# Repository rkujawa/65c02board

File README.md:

# 65c02board
Another 65c02 hobby computer

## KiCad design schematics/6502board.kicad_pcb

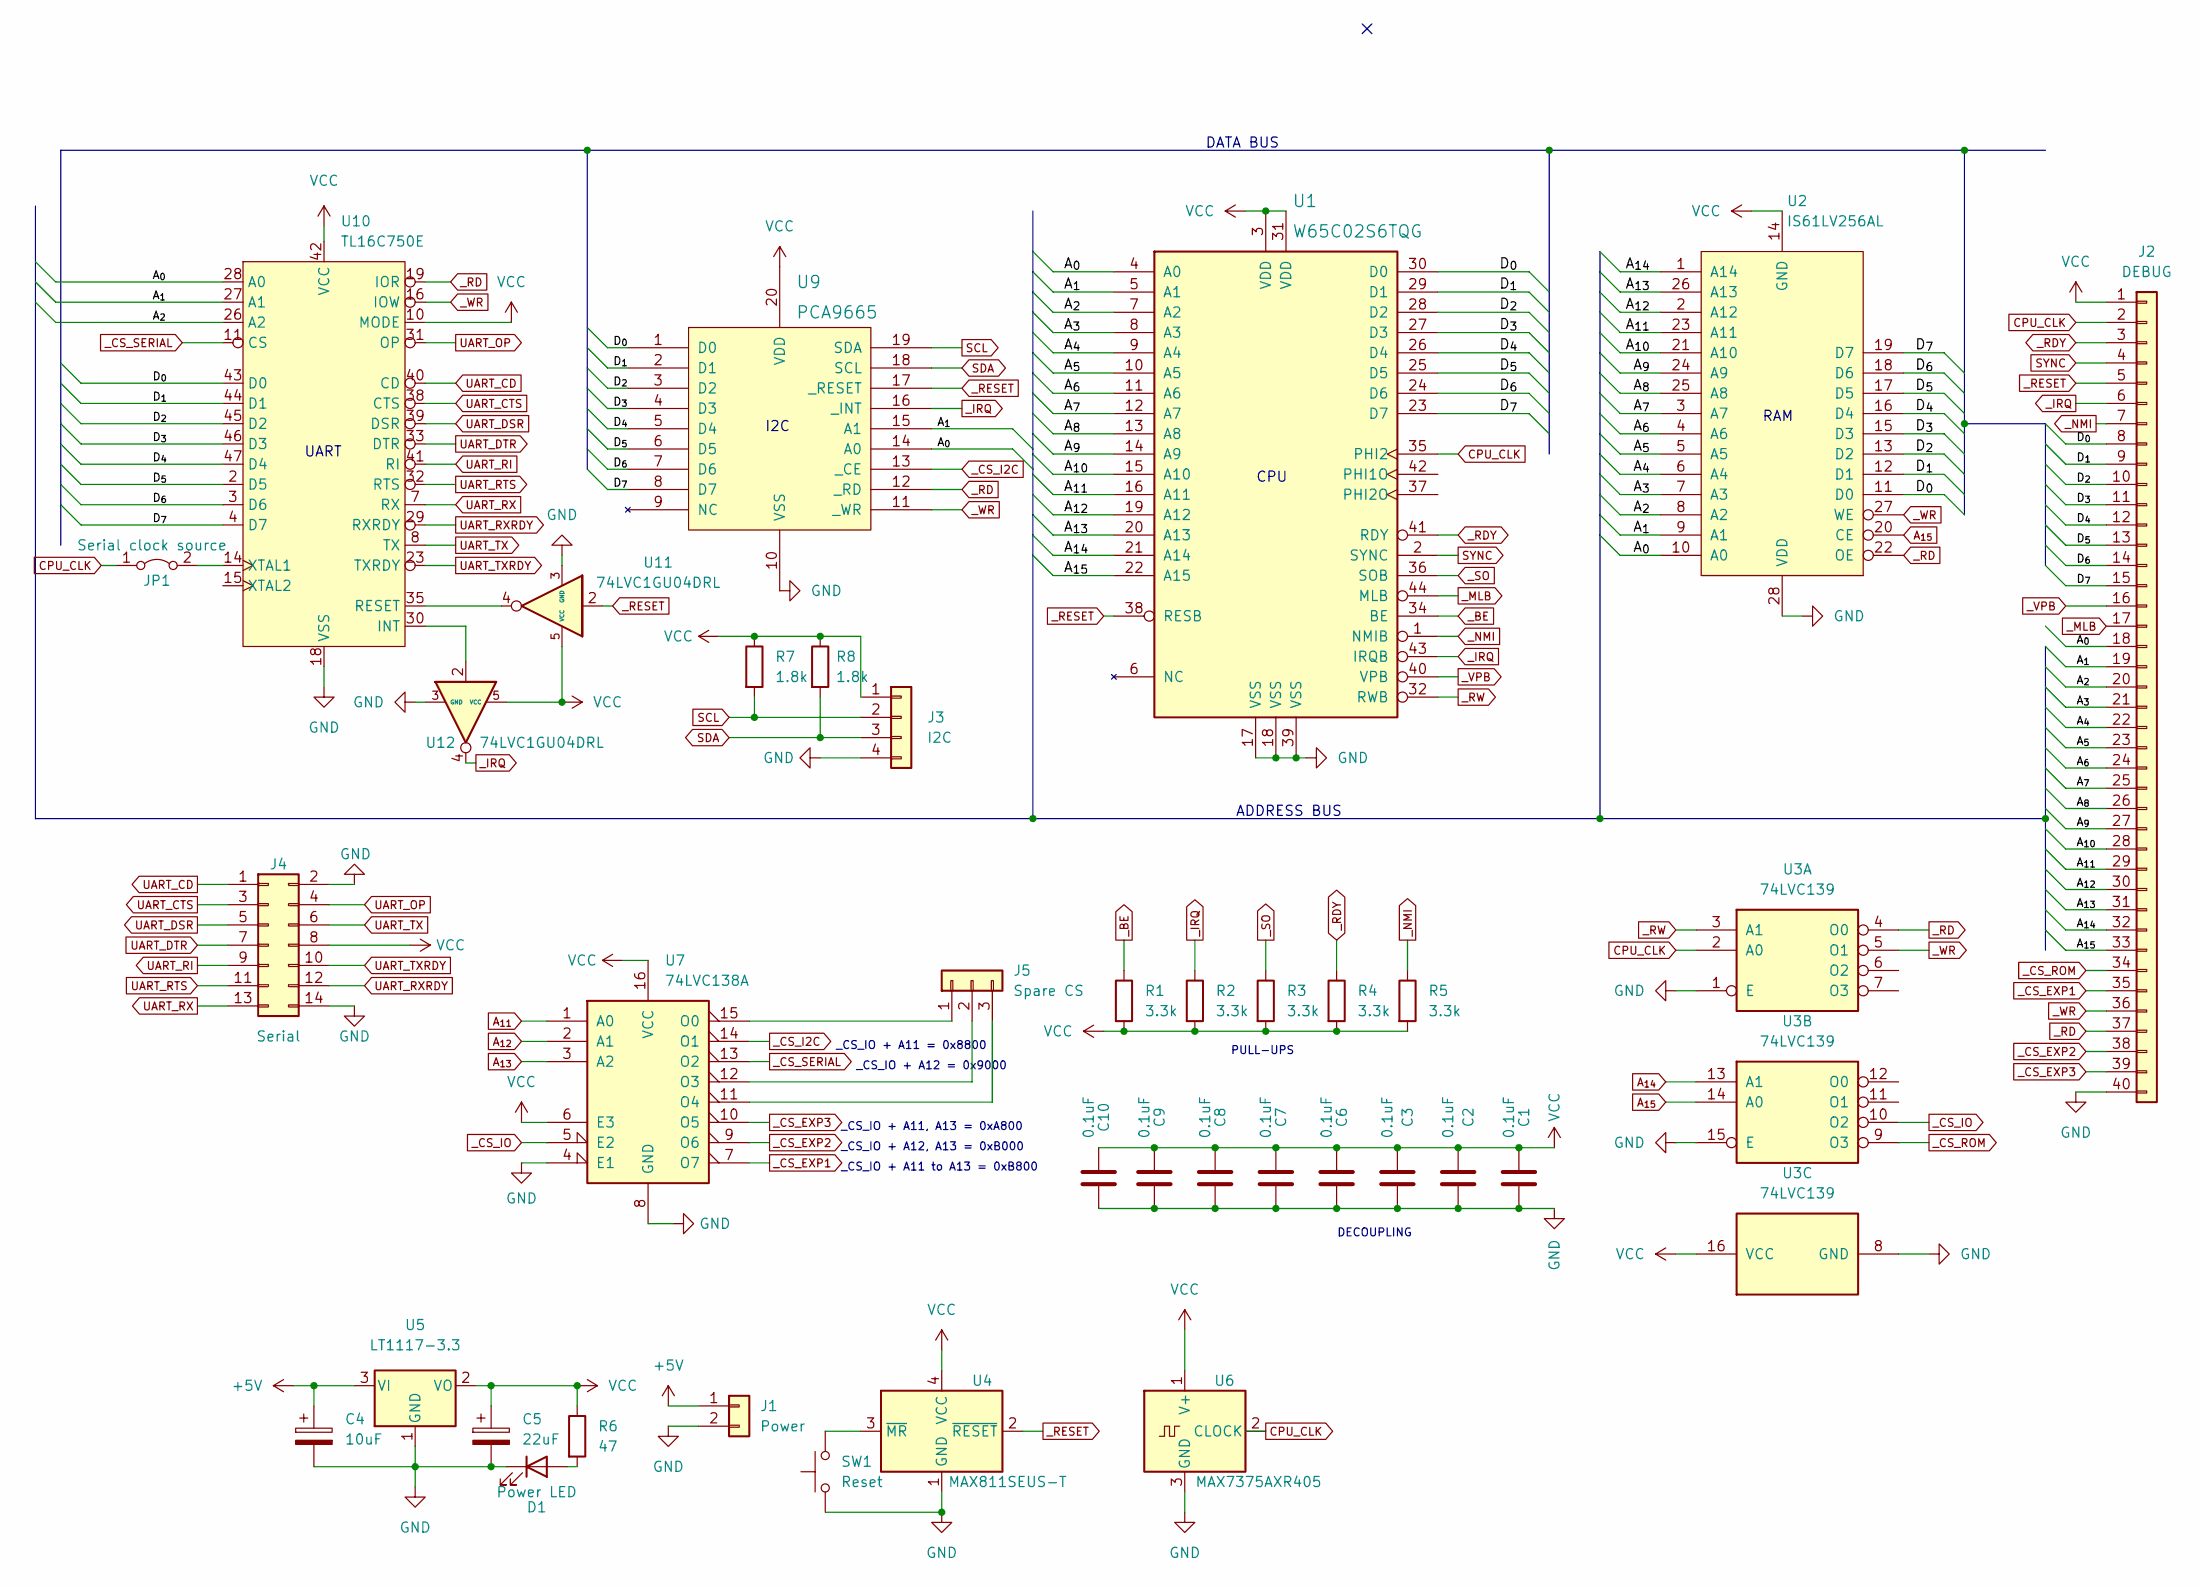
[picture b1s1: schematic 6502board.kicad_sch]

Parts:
C1, C2, C3, C6, C7, C8, C9, C10: 0.1uF; C_0805_2012Metric_Pad1.18x1.45mm_HandSolder
C4: 10uF; CP_EIA-1608-08_AVX-J_Pad1.25x1.05mm_HandSolder
C5: 22uF; CP_EIA-1608-08_AVX-J_Pad1.25x1.05mm_HandSolder
D1: Power LED; LED_1206_3216Metric_Pad1.42x1.75mm_HandSolder
J1: Power; PinHeader_1x02_P2.54mm_Vertical
J2: DEBUG; PinHeader_1x40_P2.54mm_Vertical
J3: I2C; PinHeader_1x04_P2.54mm_Vertical
J4: Serial; PinHeader_2x07_P2.54mm_Vertical
J5: Spare CS; PinHeader_1x03_P2.54mm_Vertical
JP1: Serial clock source; PinHeader_1x02_P2.54mm_Vertical
R1, R2, R3, R4, R5: 3.3k; R_0805_2012Metric_Pad1.20x1.40mm_HandSolder
R6: 47; R_1206_3216Metric_Pad1.30x1.75mm_HandSolder
R7, R8: 1.8k; R_1206_3216Metric_Pad1.30x1.75mm_HandSolder
SW1: Reset; SW_SPST_B3U-1000P
U1: W65C02S6TQG; TQFP-44_10x10mm_P0.8mm
U2: IS61LV256AL; TSOP-I-28_11.8x8mm_P0.55mm
U3: 74LVC139; TSSOP-16_4.4x5mm_P0.65mm
U4: MAX811SEUS-T; SOT-143
U5: LT1117-3.3; SOT-223-3_TabPin2
U6: MAX7375AXR405; SOT-323_SC-70
U7: 74LVC138A; TSSOP-16_4.4x5mm_P0.65mm
U9: PCA9665; TSSOP-20_4.4x6.5mm_P0.65mm
U10: TL16C750E; TQFP-48_7x7mm_P0.5mm
U11, U12: 74LVC1GU04DRL; SOT-553

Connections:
+5V: C4.1, J1.1, U5.3 (VI)
/A_{0}: J2.18, U1.4 (A0), U2.10 (A0), U9.14 (A0), U10.28 (A0)
/A_{1}: J2.19, U1.5 (A1), U2.9 (A1), U9.15 (A1), U10.27 (A1)
/A_{2}: J2.20, U1.7 (A2), U2.8 (A2), U10.26 (A2)
/A_{3}: J2.21, U1.8 (A3), U2.7 (A3)
/A_{4}: J2.22, U1.9 (A4), U2.6 (A4)
/A_{5}: J2.23, U1.10 (A5), U2.5 (A5)
/A_{6}: J2.24, U1.11 (A6), U2.4 (A6)
/A_{7}: J2.25, U1.12 (A7), U2.3 (A7)
/A_{8}: J2.26, U1.13 (A8), U2.25 (A8)
/A_{9}: J2.27, U1.14 (A9), U2.24 (A9)
/A_{10}: J2.28, U1.15 (A10), U2.21 (A10)
/D_{0}: J2.8, U1.30 (D0), U2.11 (D0), U9.1 (D0), U10.43 (D0)
/D_{1}: J2.9, U1.29 (D1), U2.12 (D1), U9.2 (D1), U10.44 (D1)
/D_{2}: J2.10, U1.28 (D2), U2.13 (D2), U9.3 (D2), U10.45 (D2)
/D_{3}: J2.11, U1.27 (D3), U2.15 (D3), U9.4 (D3), U10.46 (D3)
/D_{4}: J2.12, U1.26 (D4), U2.16 (D4), U9.5 (D4), U10.47 (D4)
/D_{5}: J2.13, U1.25 (D5), U2.17 (D5), U9.6 (D5), U10.2 (D5)
/D_{6}: J2.14, U1.24 (D6), U2.18 (D6), U9.7 (D6), U10.3 (D6)
/D_{7}: J2.15, U1.23 (D7), U2.19 (D7), U9.8 (D7), U10.4 (D7)
A_{11}: J2.29, U1.16 (A11), U2.23 (A11), U7.1 (A0)
A_{12}: J2.30, U1.19 (A12), U2.2 (A12), U7.2 (A1)
A_{13}: J2.31, U1.20 (A13), U2.26 (A13), U7.3 (A2)
A_{14}: J2.32, U1.21 (A14), U2.1 (A14), U3.13 (A1)
A_{15}: J2.33, U1.22 (A15), U2.20 (CE), U3.14 (A0)
CPU_CLK: J2.2, JP1.1 (A), U1.35 (PHI2), U3.2 (A0), U6.2 (CLOCK)
GND: C1.2, C2.2, C3.2, C4.2, C5.2, C6.2, C7.2, C8.2, C9.2, C10.2, D1.1 (K), J1.2, J2.40, J3.4, J4.2, J4.14, SW1.1, U1.17 (VSS), U1.18 (VSS), U1.39 (VSS), U2.28 (VDD), U3.1 (E), U3.8 (GND), U3.15 (E), U4.1 (GND), U5.1 (GND), U6.3 (GND), U7.4 (E1), U7.8 (GND), U9.10 (VSS), U10.18 (VSS), U11.3 (GND), U12.3 (GND)
unnamed: D1.2 (A), R6.2
unnamed: J5.1, U7.15 (O0)
unnamed: J5.2, U7.12 (O3)
unnamed: J5.3, U7.11 (O4)
unnamed: JP1.2 (B), U10.14 (XTAL1)
unnamed: SW1.2, U4.3 (~MR)
unnamed: U10.35 (RESET), U11.4
unnamed: U10.30 (INT), U12.2
SCL: J3.2, R7.2, U9.19 (SDA)
SDA: J3.3, R8.2, U9.18 (SCL)
SYNC: J2.4, U1.2 (SYNC)
UART_CD: J4.1, U10.40 (CD)
UART_CTS: J4.3, U10.38 (CTS)
UART_DSR: J4.5, U10.39 (DSR)
UART_DTR: J4.7, U10.33 (DTR)
UART_OP: J4.4, U10.31 (OP)
UART_RI: J4.9, U10.41 (RI)
UART_RTS: J4.11, U10.32 (RTS)
UART_RX: J4.13, U10.7 (RX)
UART_RXRDY: J4.12, U10.29 (RXRDY)
UART_TX: J4.6, U10.8 (TX)
UART_TXRDY: J4.10, U10.23 (TXRDY)
VCC: C1.1, C2.1, C3.1, C5.1, C6.1, C7.1, C8.1, C9.1, C10.1, J2.1, J3.1, J4.8, R1.2, R2.2, R3.2, R4.2, R5.2, R6.1, R7.1, R8.1, U1.3 (VDD), U1.31 (VDD), U2.14 (GND), U3.16 (VCC), U4.4 (VCC), U5.2 (VO), U6.1 (V+), U7.6 (E3), U7.16 (VCC), U9.20 (VDD), U10.10 (MODE), U10.42 (VCC), U11.5 (VCC), U12.5 (VCC)
_BE: R1.1, U1.34 (BE)
_CS_EXP1: J2.35, U7.7 (O7)
_CS_EXP2: J2.38, U7.9 (O6)
_CS_EXP3: J2.39, U7.10 (O5)
_CS_I2C: U7.14 (O1), U9.13 (_CE)
_CS_IO: U3.10 (O2), U7.5 (E2)
_CS_ROM: J2.34, U3.9 (O3)
_CS_SERIAL: U7.13 (O2), U10.11 (CS)
_IRQ: J2.6, R2.1, U1.43 (IRQB), U9.16 (_INT), U12.4
_MLB: J2.17, U1.44 (MLB)
_NMI: J2.7, R5.1, U1.1 (NMIB)
_RD: J2.37, U2.22 (OE), U3.4 (O0), U9.12 (_RD), U10.19 (IOR)
_RDY: J2.3, R4.1, U1.41 (RDY)
_RESET: J2.5, U1.38 (RESB), U4.2 (~RESET), U9.17 (_RESET), U11.2
_RW: U1.32 (RWB), U3.3 (A1)
_SO: R3.1, U1.36 (SOB)
_VPB: J2.16, U1.40 (VPB)
_WR: J2.36, U2.27 (WE), U3.5 (O1), U9.11 (_WR), U10.16 (IOW)

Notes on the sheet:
UART
I2C
_CS_IO + A11, A13 = 0xA800
_CS_IO + A12 = 0x9000
DATA BUS
CPU
DECOUPLING
ADDRESS BUS
_CS_IO + A11 = 0x8800
_CS_IO + A11 to A13 = 0xB800
PULL-UPS
_CS_IO + A12, A13 = 0xB000
RAM

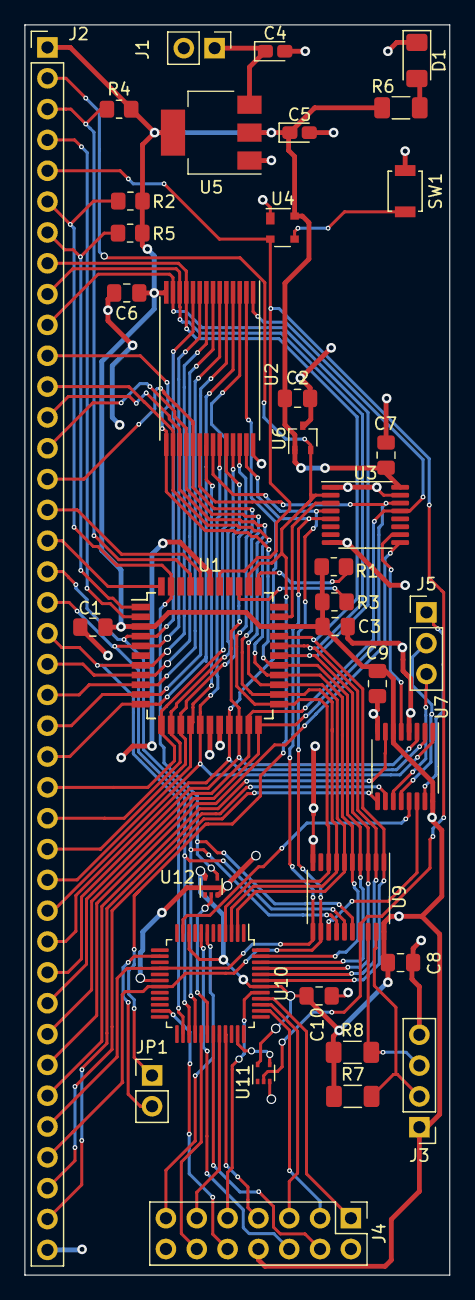
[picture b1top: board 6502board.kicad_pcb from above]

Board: 2 copper layers, 35.0 x 103.0 mm, 37 parts (0 on the bottom side), 68 nets.

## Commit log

2023-01-21 Initial import of schematics and pcb design.
2023-01-22 Invert IRQ and RESET for UART. Experiment with vias.
